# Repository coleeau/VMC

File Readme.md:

# Versatile Micro Computer

The Versatile Micro Computer (VMC for short) is a 6502 platform designed to be Powerful, expandable, and versatile

The VMC was designed as a project to express everything I have leared in electrical engineering,
and as a way to learn more concepts in electrical engineering, computer engineering and computer science

## Repository layout

- Hardware: KiCad files for the Hardware side of the VMC
- Reference: Reference documents
- Software: all sorts of programs
- Tools: Tools for testing

## Licensing

- Hardware: Global License applies to all files
- Reference: License depends on file. Global license likely applies to any non datasheet files.
- Software: Global License applies to all files outside of /3rd Party Software/ folder
- Tools: Global License does not apply to any file.

## Roadmap

### Complete

- Design of Revision 1 Arcitecture
- Revision 1 PCB Layout
- Bootstrap Program "Rudimentery"
- Assemble and
### In Progress

- Test Revision 1 Hardware
- Write Bios

### Planned

- Port Basic
- Replace glue logic with PLD for better speed and cost efficiancy

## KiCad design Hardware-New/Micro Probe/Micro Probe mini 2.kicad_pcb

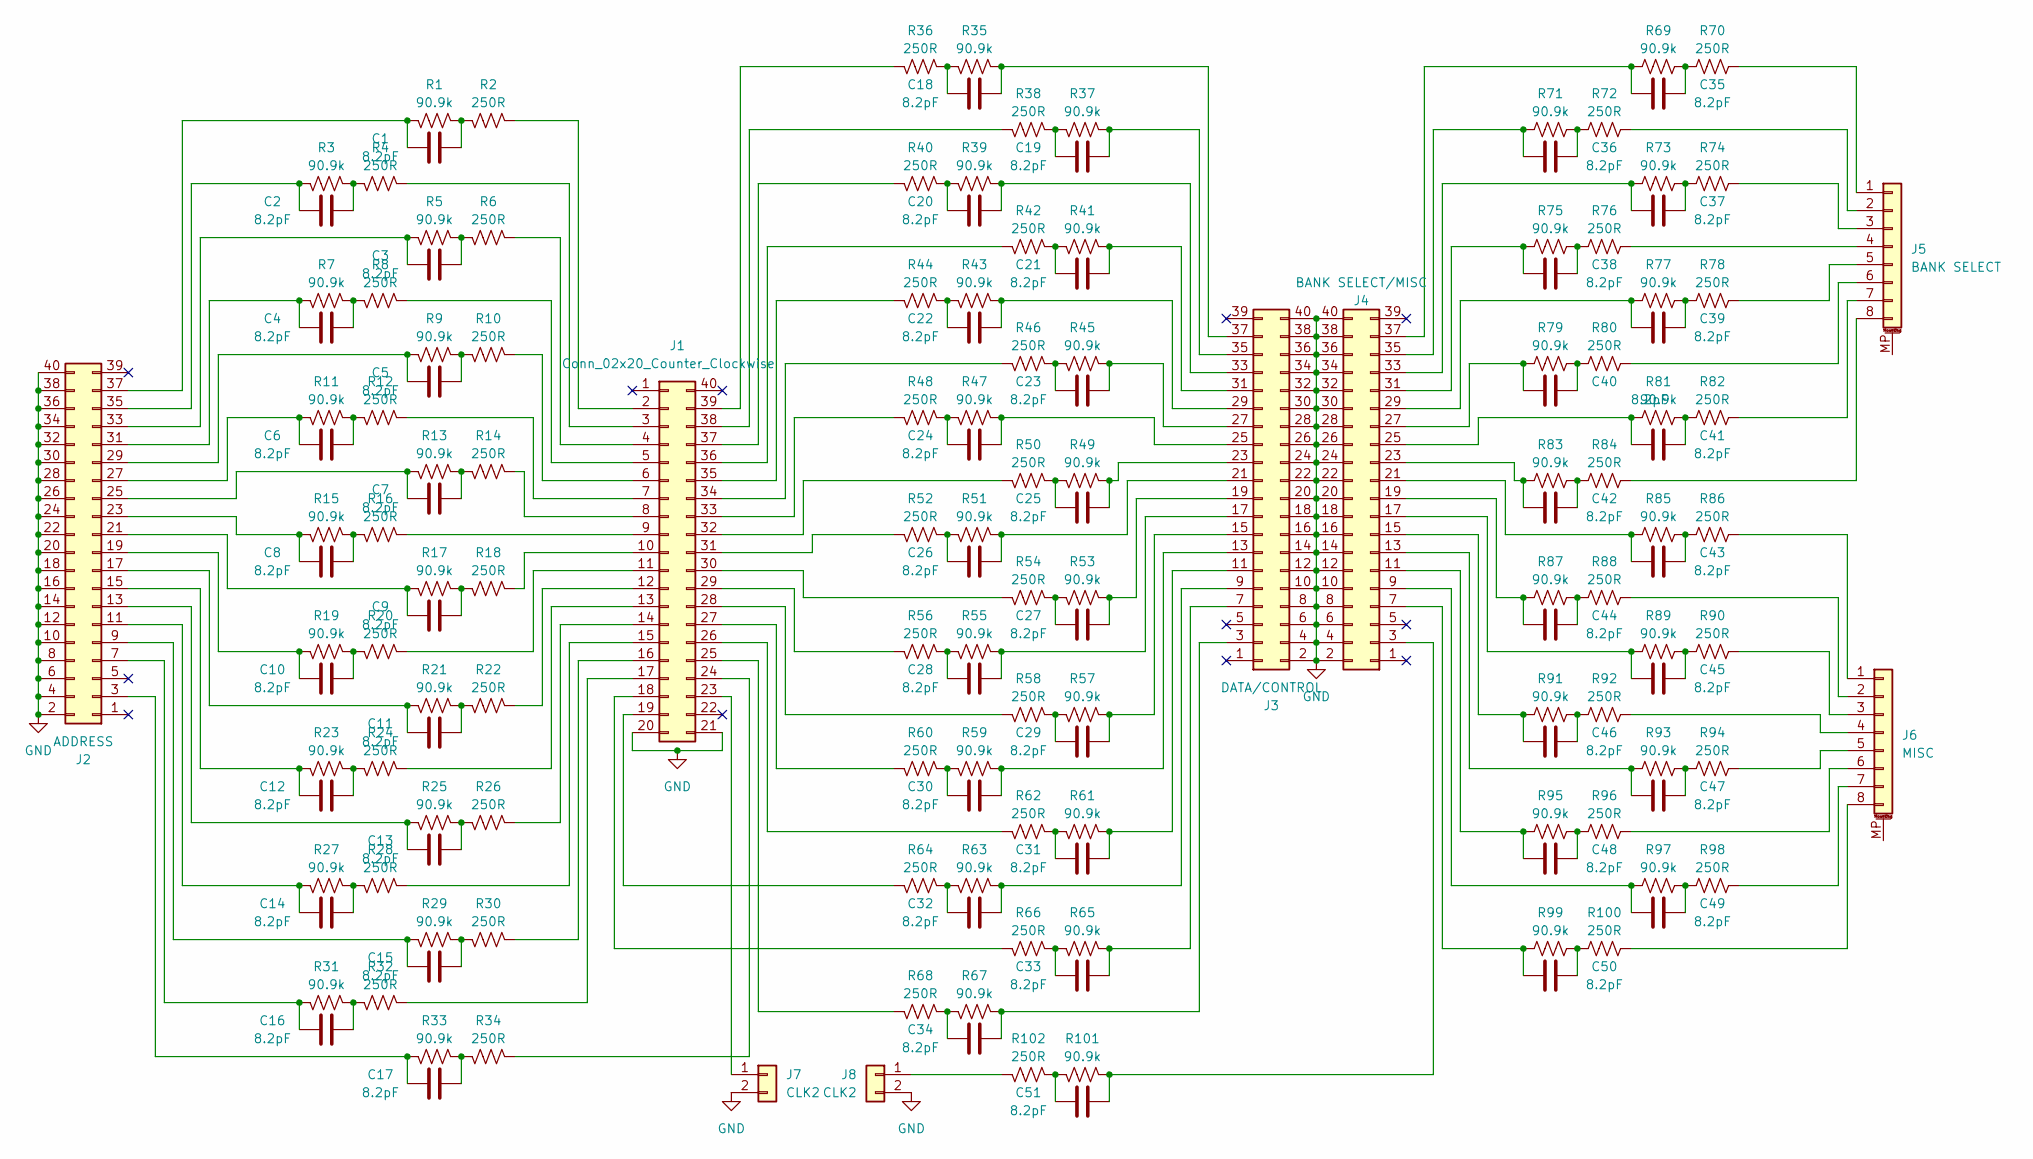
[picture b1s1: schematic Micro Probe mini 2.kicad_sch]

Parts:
C1, C2, C3, C4, C5, C6, C7, C8, C9, C10, C11, C12, C13, C14, C15, C16, C17, C18, C19, C20, C21, C22, C23, C24, C25, C26, C27, C28, C29, C30, C31, C32, C33, C34, C35, C36, C37, C38, C39, C40, C41, C42, C43, C44, C45, C46, C47, C48, C49, C50, C51: 8.2pF; R_0603_1608Metric
J1: Conn_02x20_Counter_Clockwise; PinHeader_2x20_P2.54mm_Vertical
J2: ADDRESS; PinHeader_2x20_P2.54mm_Vertical
J3: DATA/CONTROL; PinHeader_2x20_P2.54mm_Vertical
J4: BANK SELECT/MISC; PinHeader_2x20_P2.54mm_Vertical
J5: BANK SELECT; JST_SH_SM08B-SRSS-TB_1x08-1MP_P1.00mm_Horizontal
J6: MISC; JST_SH_SM08B-SRSS-TB_1x08-1MP_P1.00mm_Horizontal
J7, J8: CLK2; JST_SH_SM02B-SRSS-TB_1x02-1MP_P1.00mm_Horizontal
R1, R3, R5, R7, R9, R11, R13, R15, R17, R19, R21, R23, R25, R27, R29, R31, R33, R35, R37, R39, R41, R43, R45, R47, R49, R51, R53, R55, R57, R59, R61, R63, R65, R67, R69, R71, R73, R75, R77, R79, R81, R83, R85, R87, R89, R91, R93, R95, R97, R99, R101: 90.9k; R_0603_1608Metric
R2, R4, R6, R8, R10, R12, R14, R16, R18, R20, R22, R24, R26, R28, R30, R32, R34, R36, R38, R40, R42, R44, R46, R48, R50, R52, R54, R56, R58, R60, R62, R64, R66, R68, R70, R72, R74, R76, R78, R80, R82, R84, R86, R88, R90, R92, R94, R96, R98, R100, R102: 250R; R_0603_1608Metric

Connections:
GND: J1.20, J1.21, J2.2, J2.4, J2.6, J2.8, J2.10, J2.12, J2.14, J2.16, J2.18, J2.20, J2.22, J2.24, J2.26, J2.28, J2.30, J2.32, J2.34, J2.36, J2.38, J2.40, J3.2, J3.4, J3.6, J3.8, J3.10, J3.12, J3.14, J3.16, J3.18, J3.20, J3.22, J3.24, J3.26, J3.28, J3.30, J3.32, J3.34, J3.36, J3.38, J3.40, J4.2, J4.4, J4.6, J4.8, J4.10, J4.12, J4.14, J4.16, J4.18, J4.20, J4.22, J4.24, J4.26, J4.28, J4.30, J4.32, J4.34, J4.36, J4.38, J4.40, J5.MP (MountPin), J6.MP (MountPin), J7.2, J7.MP, J8.2, J8.MP
unnamed: C1.1, R1.1, R2.2
unnamed: C2.1, R3.1, R4.2
unnamed: C3.1, R5.1, R6.2
unnamed: C4.1, R7.1, R8.2
unnamed: C5.1, R9.1, R10.2
unnamed: C6.1, R11.1, R12.2
unnamed: C7.1, R13.1, R14.2
unnamed: C8.1, R15.1, R16.2
unnamed: C9.1, R17.1, R18.2
unnamed: C10.1, R19.1, R20.2
unnamed: C11.1, R21.1, R22.2
unnamed: C12.1, R23.1, R24.2
unnamed: C13.1, R25.1, R26.2
unnamed: C14.1, R27.1, R28.2
unnamed: C15.1, R29.1, R30.2
unnamed: C16.1, R31.1, R32.2
unnamed: C17.1, R33.1, R34.2
unnamed: C18.2, R35.2, R36.1
unnamed: C19.2, R37.2, R38.1
unnamed: C20.2, R39.2, R40.1
unnamed: C21.2, R41.2, R42.1
unnamed: C22.2, R43.2, R44.1
unnamed: C23.2, R45.2, R46.1
unnamed: C24.2, R47.2, R48.1
unnamed: C25.2, R49.2, R50.1
unnamed: C26.2, R51.2, R52.1
unnamed: C27.2, R53.2, R54.1
unnamed: C28.2, R55.2, R56.1
unnamed: C29.2, R57.2, R58.1
unnamed: C30.2, R59.2, R60.1
unnamed: C31.2, R61.2, R62.1
unnamed: C32.2, R63.2, R64.1
unnamed: C33.2, R65.2, R66.1
unnamed: C34.2, R67.2, R68.1
unnamed: C35.2, R69.2, R70.1
unnamed: C36.2, R71.2, R72.1
unnamed: C37.2, R73.2, R74.1
unnamed: C38.2, R75.2, R76.1
unnamed: C39.2, R77.2, R78.1
unnamed: C40.2, R79.2, R80.1
unnamed: C41.2, R81.2, R82.1
unnamed: C42.2, R83.2, R84.1
unnamed: C43.2, R85.2, R86.1
unnamed: C44.2, R87.2, R88.1
unnamed: C45.2, R89.2, R90.1
unnamed: C46.2, R91.2, R92.1
unnamed: C47.2, R93.2, R94.1
unnamed: C48.2, R95.2, R96.1
unnamed: C49.2, R97.2, R98.1
unnamed: C50.2, R99.2, R100.1
unnamed: C51.2, R101.2, R102.1
unnamed: J1.2, R2.1
unnamed: J1.3, R4.1
unnamed: J1.4, R6.1
unnamed: J1.5, R8.1
unnamed: J1.6, R10.1
unnamed: J1.7, R12.1
unnamed: J1.8, R14.1
unnamed: J1.9, R16.1
unnamed: J1.10, R18.1
unnamed: J1.11, R20.1
unnamed: J1.12, R22.1
unnamed: J1.13, R24.1
unnamed: J1.14, R26.1
unnamed: J1.15, R28.1
unnamed: J1.16, R30.1
unnamed: J1.17, R32.1
unnamed: J1.18, R66.2
unnamed: J1.19, R64.2
unnamed: J1.23, J7.1
unnamed: J1.24, R34.1
unnamed: J1.25, R68.2
unnamed: J1.26, R62.2
unnamed: J1.27, R60.2
unnamed: J1.28, R58.2
unnamed: J1.29, R56.2
unnamed: J1.30, R54.2
unnamed: J1.31, R52.2
unnamed: J1.32, R50.2
unnamed: J1.33, R48.2
unnamed: J1.34, R46.2
unnamed: J1.35, R44.2
unnamed: J1.36, R42.2
unnamed: J1.37, R40.2
unnamed: J1.38, R38.2
unnamed: J1.39, R36.2
unnamed: C17.2, J2.3, R33.2
unnamed: C16.2, J2.7, R31.2
unnamed: C15.2, J2.9, R29.2
unnamed: C14.2, J2.11, R27.2
unnamed: C13.2, J2.13, R25.2
unnamed: C12.2, J2.15, R23.2
unnamed: C11.2, J2.17, R21.2
unnamed: C10.2, J2.19, R19.2
unnamed: C9.2, J2.21, R17.2
unnamed: C8.2, J2.23, R15.2
unnamed: C7.2, J2.25, R13.2
unnamed: C6.2, J2.27, R11.2
unnamed: C5.2, J2.29, R9.2
unnamed: C4.2, J2.31, R7.2
unnamed: C3.2, J2.33, R5.2
unnamed: C2.2, J2.35, R3.2
unnamed: C1.2, J2.37, R1.2
unnamed: C34.1, J3.3, R67.1
unnamed: C33.1, J3.7, R65.1
unnamed: C32.1, J3.9, R63.1
unnamed: C31.1, J3.11, R61.1
unnamed: C30.1, J3.13, R59.1
unnamed: C29.1, J3.15, R57.1
unnamed: C28.1, J3.17, R55.1
unnamed: C27.1, J3.19, R53.1
unnamed: C26.1, J3.21, R51.1
unnamed: C25.1, J3.23, R49.1
unnamed: C24.1, J3.25, R47.1
unnamed: C23.1, J3.27, R45.1
unnamed: C22.1, J3.29, R43.1
unnamed: C21.1, J3.31, R41.1
unnamed: C20.1, J3.33, R39.1
unnamed: C19.1, J3.35, R37.1
unnamed: C18.1, J3.37, R35.1
unnamed: C51.1, J4.3, R101.1
unnamed: C50.1, J4.7, R99.1
unnamed: C49.1, J4.9, R97.1
unnamed: C48.1, J4.11, R95.1
unnamed: C47.1, J4.13, R93.1
unnamed: C46.1, J4.15, R91.1
unnamed: C45.1, J4.17, R89.1
unnamed: C44.1, J4.19, R87.1
unnamed: C43.1, J4.21, R85.1
unnamed: C42.1, J4.23, R83.1
unnamed: C41.1, J4.25, R81.1
unnamed: C40.1, J4.27, R79.1
unnamed: C39.1, J4.29, R77.1
unnamed: C38.1, J4.31, R75.1
unnamed: C37.1, J4.33, R73.1
unnamed: C36.1, J4.35, R71.1
unnamed: C35.1, J4.37, R69.1
unnamed: J5.1, R70.2
unnamed: J5.2, R72.2
unnamed: J5.3, R74.2
unnamed: J5.4, R76.2
unnamed: J5.5, R78.2
unnamed: J5.6, R80.2
unnamed: J5.7, R82.2
unnamed: J5.8, R84.2
unnamed: J6.1, R86.2
unnamed: J6.2, R88.2
unnamed: J6.3, R90.2
unnamed: J6.4, R92.2
unnamed: J6.5, R94.2
unnamed: J6.6, R96.2
unnamed: J6.7, R98.2
unnamed: J6.8, R100.2
unnamed: J8.1, R102.2

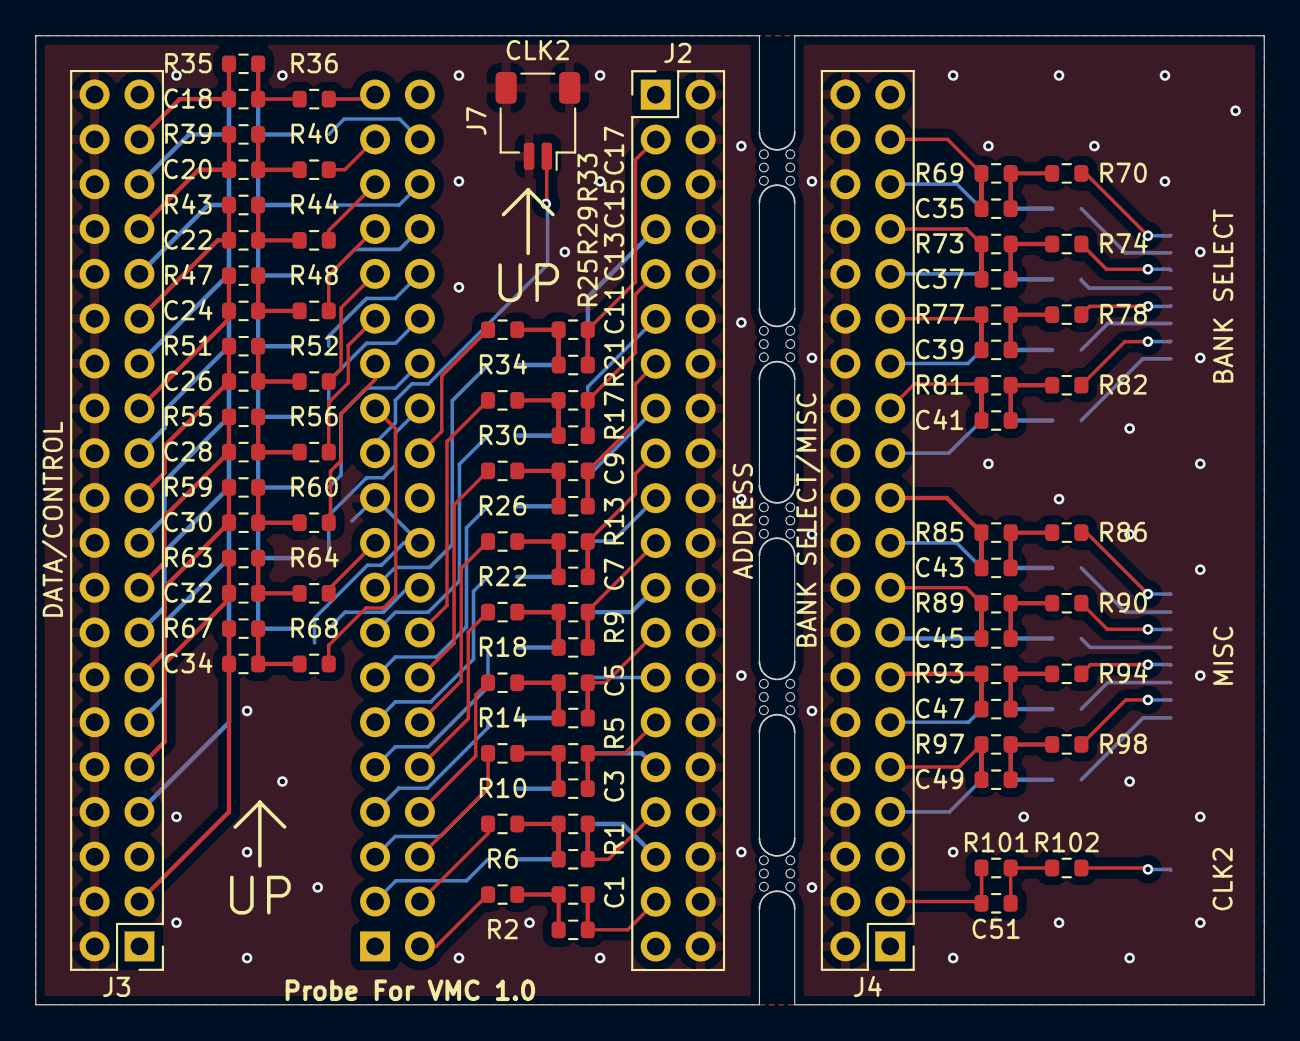
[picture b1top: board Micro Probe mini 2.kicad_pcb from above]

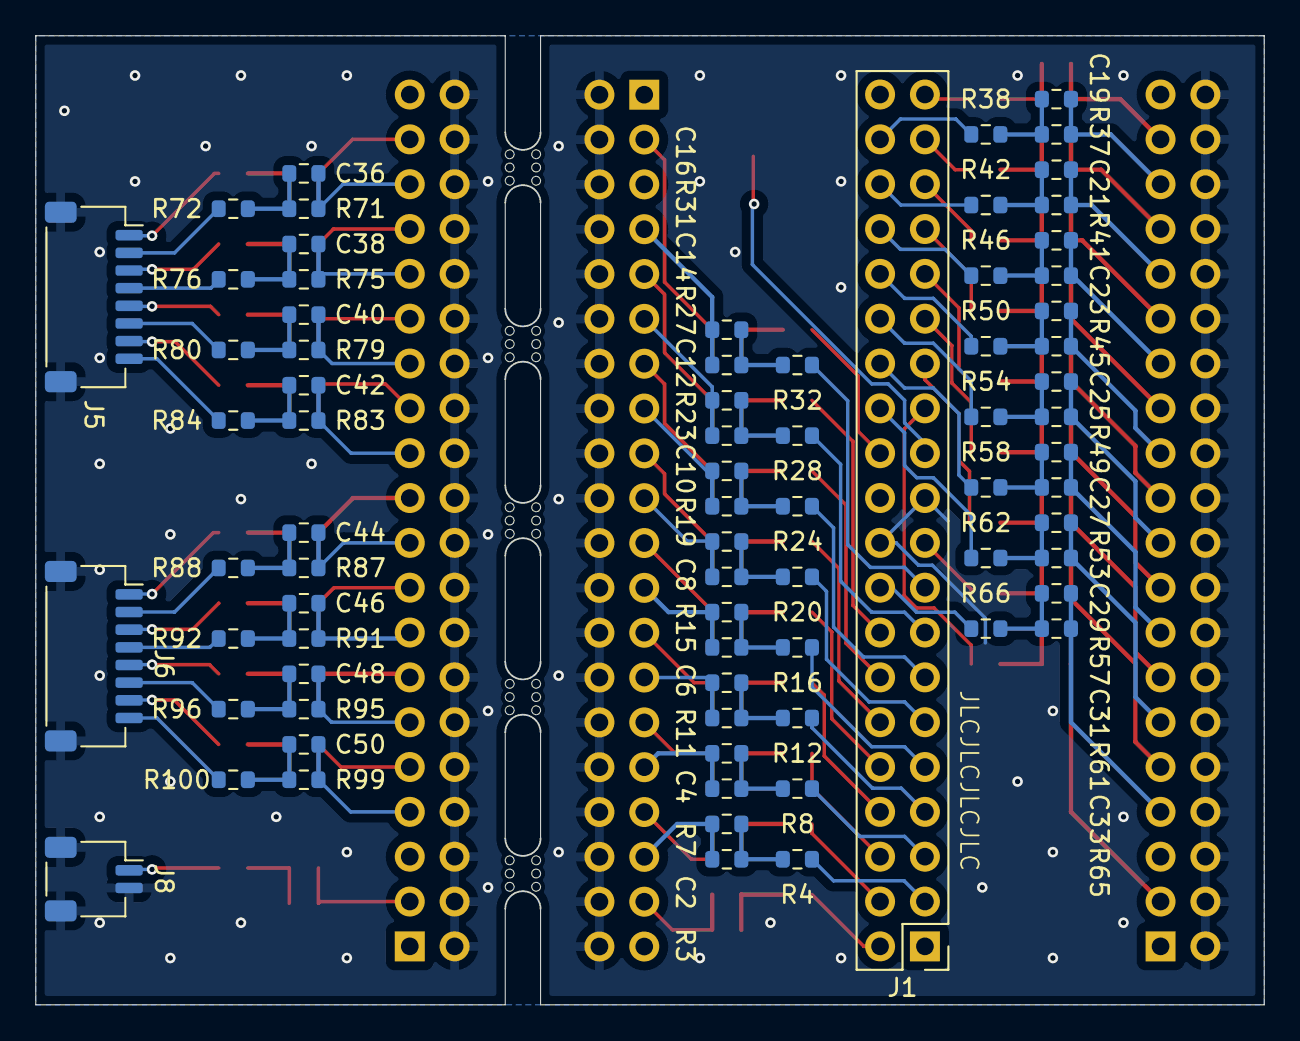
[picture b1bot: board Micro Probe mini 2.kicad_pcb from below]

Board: 2 copper layers, 69.5 x 54.8 mm, 166 parts (76 on the bottom side), 155 nets.

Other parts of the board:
mouse-bite-2mm-slot, mouse-bite-2mm-slot#2, mouse-bite-2mm-slot#3, mouse-bite-2mm-slot#4, mouse-bite-2mm-slot#5: VAL**; mouse-bite-2mm-slot

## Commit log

2023-12-22 time at which file control was changed from renaming files to actually using git revisions prior to this are under /BAK
2023-12-22 converting to git
2023-12-23 adjusted instruction ordering fixed incorrect jmp/bra instructions changed nmos to use beq in places due to zero flag always being true removed a stz that happened right after ram cleared to zero cha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
2023-12-23 Restructuring, adding hardware to repository
    make_opti.bat directories adjusted for changes
2023-12-23 Added Readme.md
2023-12-23 Readme.md: Spell checking
2023-12-23 Fixing Readme.md by changing somethings to bulleted lists
2024-01-03 Created file for Bios
2024-01-03 added most plans for what will be bios routines
2024-01-04 Starting to write Main ISR routine
2024-01-04 Finished Main IRQ routine (sans external IRQ)
2024-01-05 Added 8bit Multi and Div routines
2024-01-06 Added definition file of JDRLE (an rle format by me that i will be working on)
2024-01-08 Added Hardware Documentation under /Reference
    Wrote single Char TX and RX routine
2024-01-09 Added to Bios B_RX_Char B_TX_Char B_COMM_Set_Speed All BankSwitch routines B_Nybble_Swap B_VER
    also Added Some of the i2c routines
    I2C_Init (for routine)
    I2C_Main
    I2C_Write
    I2C_Ack_Read
    added project for Si5351a
2024-01-09 added pll register map
2024-01-10 Adjusted I2C_Ack_Nack_Write to use I2C_Write routine
2024-01-10 weird. idk why it made me change it
2024-01-10 Added I2C_Read and converted I2C_Read_Ack to use I2C_Read routine
2024-01-10 Added B_COMM_TX_Char and B_COMM_TX_STR
2024-01-10 Added B_TIME_Count and irq handling of timer
    timing.txt: info on timer counting abilities
    Added wdc programming manual: Programmingthe65816_ProgManual 1986.pdf
    added additional register file for when out2 is at 2 MHz: VCM-Registersout2.h
2024-01-11 Hardware: fixed error in schematic with clock moved dotclock to out 2 (better for jitter) allowed the replacement of 82c54 CPU CLK with CLK 2 moved nmi switch to a more reasonable location
2024-01-11 Hardware: fixed error in schematic with clock moved dotclock to out 2 (better for jitter) allowed the replacement of 82c54 CPU CLK with CLK 2 moved nmi switch to a more reasonable location
    software:
    added timing info to count subroutine
    Reference:
    Added documentation on si5351 registers
2024-01-13 added comments to i2c routine
2024-01-13 B_TIME_Delay: replaced ROL SEC ROR with TSB (save 5 cycles 2bytes)
    B_COMM_Set_Speed: replace ADC STA with TSB (2 cycles, 3 bytes)
    Replace LDA SEC SBC STA 12 with LDA TRB (4 cycles, 5 bytes)
2024-01-13 Fixed error in TIE LE signal (Logic was inverted, replaced or with nor)
2024-01-13 test
2024-01-14 test 2
2024-01-14 Added B_Add_16, B_Sub_16,
    started work on 2 varients of B_Panic
    1 that affects no memory, one that affects 0200-0204
2024-01-16 test 3
2024-01-16 Further work on Panic
2024-01-16 More MORE WORK on Panic
2024-01-22 Finallized board, added jumpers for debug, added reset to Ext connector other errors fixed
2024-01-22 Bios: B_COMM_TX_Char changed to wait until Char is sent in order to exit B_COMM_MoveCsr vt100 move cursor command added B_ReadKey Added command to read key to buffer @$0200 Fixed error in B_TIME_Dela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
    Added missing STA to IRQ-Timer
    Started on IRQ_COMM
    added IRQ_Key Routine
2024-01-24 BIOS: Continued Entrypoint Cold from Entrypoint_Test_CLK to Entrypoint_Done added more Entrypoint strings Added B_COMM_ClsScr (vt100 clear screen)
2024-01-24 Added writeup on MON commands
2024-02-05 set up boms
2024-02-05 Bios: ZP mapping changed fixing incorrect syntax and typos Added bios jump table for bios calls (in Bios.inc) slightly renamed some functions Added I2C_Stop Added 16 bit multi+Div made sure unoccupie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
    ROM.asm: created makefile basically
    Moved documentation to /Documentation
2024-02-05 Renamed /Software/Bios To /Software/Rom
2024-02-05 corrected address for final jump in Rudimentery/rudimentery_optimized.asm
2024-02-13 Trimmed Files (.bak .o .bin)
    PLL/VCM-Design-Report.txt : updated to correct specification (as of 2/13/24)
    vmc_fe.cfg : updated to correct rom size and corrected offset
    Rudimentery/rudimentery_optimized.asm : fixed indirect jump from incorrect mem address
2024-02-14 atempt to fix git inside git
2024-02-16 Prep for merge into main repo
2024-02-16 remove hardware for attempt at fixing git lol, update README.md
2024-02-19 RLE alg.txt : slight updates Bios.asm : added a bit of info in comments RLE/RLE.asm : Started writing rle algorythm. Entrypoint and 3/5 commands are done Routines.txt : Created, reference for bios ro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
2024-02-26 RLE/RLE.asm: added mode 1, fixed errors Bios.asm: moved ZP defs to ZP.inc, added .include for RLE.asm Bios.inc: added .segment, updated B_DATA_RLE_Decode ROM.asm: Adjusted for linker vmc.cfg: adjuste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
    Sound/n163_inf.txt: info on namco 163, used for research into sound hardware
2024-03-21 RLE.asm: added start to mode 4 Micro_Probe_Pinout.xlsx : added pinout Reference/Misc/: added mascot and associated versions Tools/RLE Encode/src/: c program to encode raw binary to mode_1 rle
2024-04-11 Bios.asm: added remote echo to rx strings
    Mon.asm: Added entrypoint, mainloop, Mon_String routine
    ZP.inc: Added ZP_Mon_Bak and ZP_Bios_Flags
    Routines.txt: updated info for changes to Bios.asm
